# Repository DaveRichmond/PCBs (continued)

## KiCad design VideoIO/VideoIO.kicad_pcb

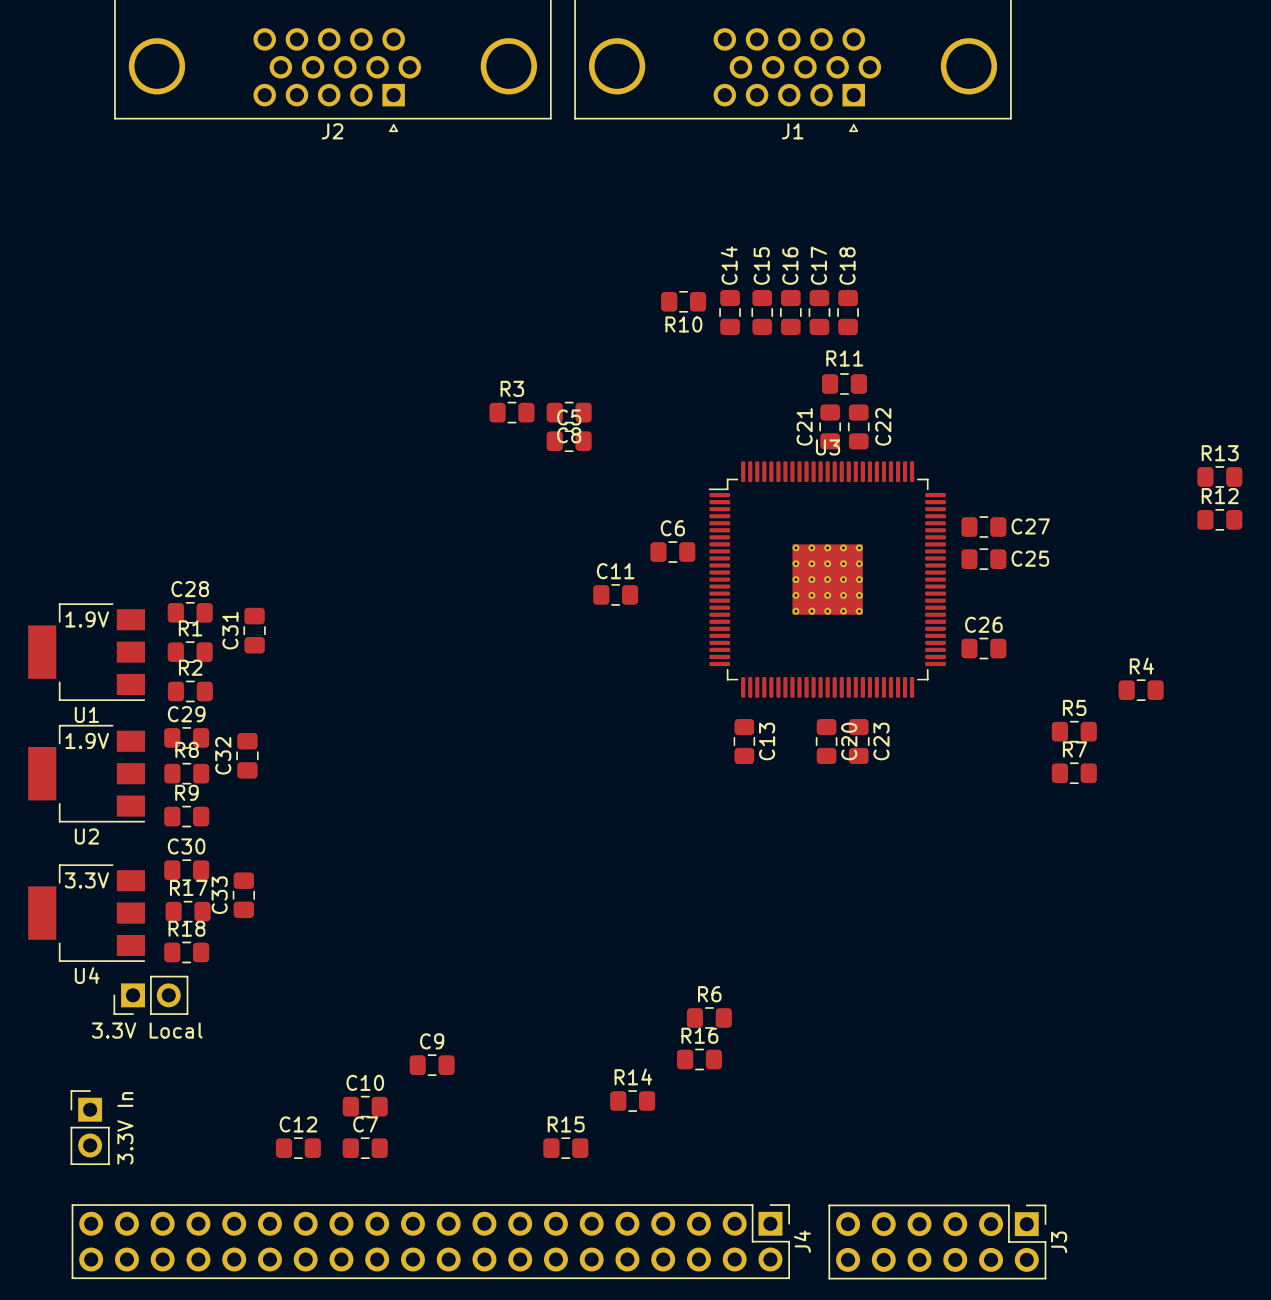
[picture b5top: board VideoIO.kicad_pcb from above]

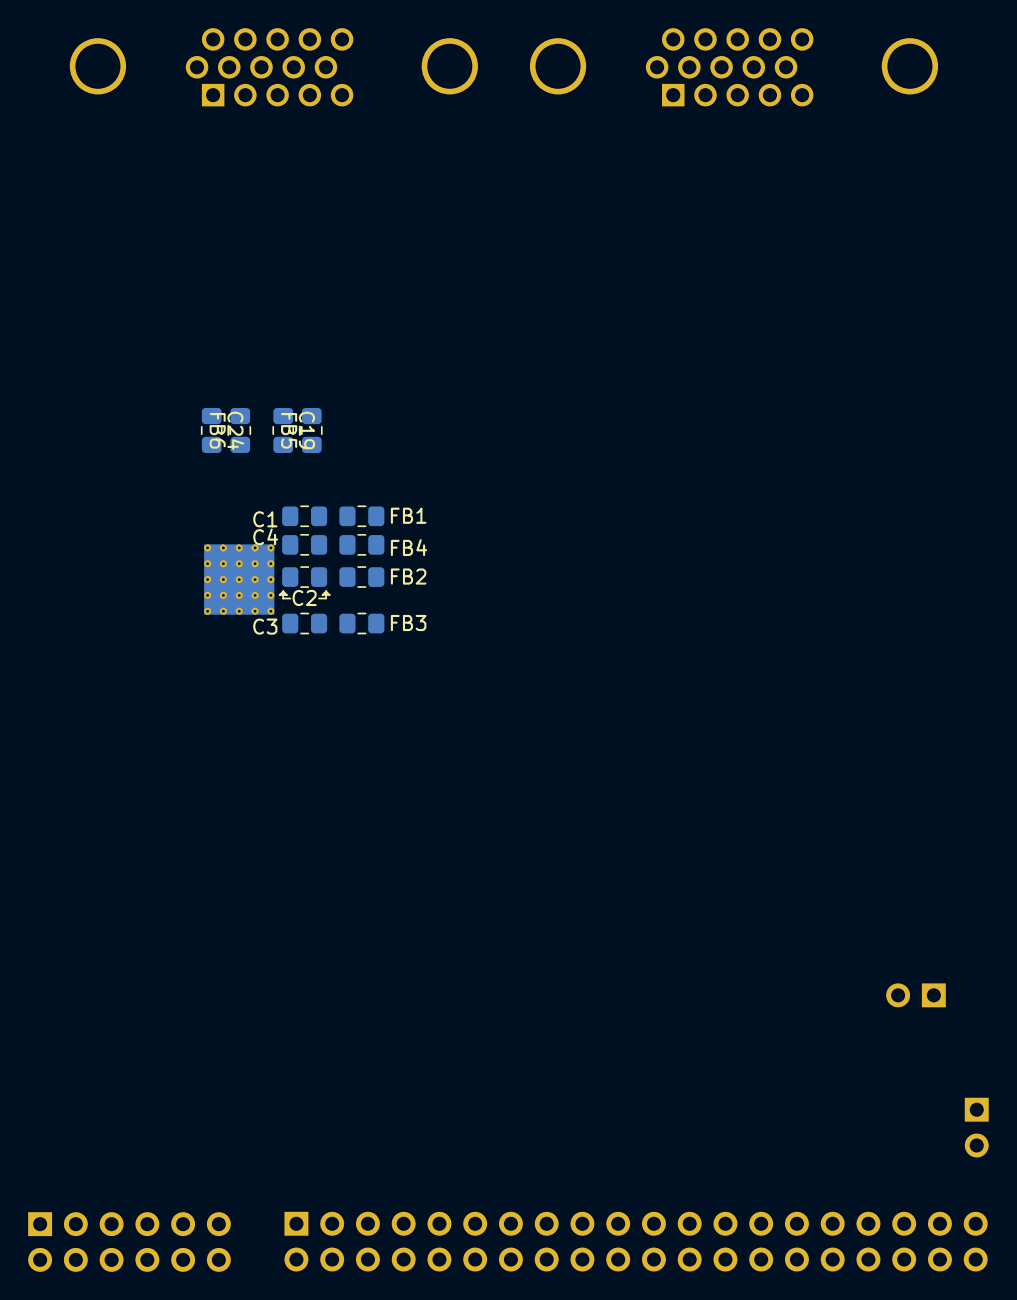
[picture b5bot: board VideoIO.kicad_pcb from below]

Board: 2 copper layers, 67 parts (12 on the bottom side), 84 nets, no tracks yet.

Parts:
C1, C2, C3, C4, C5, C6, C7, C10, C12, C13, C14, C19, C20, C22, C23, C24, C25, C26, C27: 100n; C_0805_2012Metric_Pad1.15x1.40mm_HandSolder
C8, C15, C17: 1n; C_0805_2012Metric_Pad1.15x1.40mm_HandSolder
C9, C11, C16, C18: 10n; C_0805_2012Metric_Pad1.15x1.40mm_HandSolder
C21: 4.7n; C_0805_2012Metric_Pad1.15x1.40mm_HandSolder
C28, C29, C30: C; C_0805_2012Metric_Pad1.15x1.40mm_HandSolder
C31, C32, C33: 10u; C_0805_2012Metric_Pad1.18x1.45mm_HandSolder
FB1, FB2, FB3, FB4, FB5, FB6: Ferrite_Bead_Small; L_0805_2012Metric_Pad1.15x1.40mm_HandSolder
J1, J2: DB15_Male_HighDensity; DSUB-15-HD_Male_Horizontal_P2.29x1.98mm_EdgePinOffset3.03mm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
J3: Conn_02x06_Odd_Even; PinHeader_2x06_P2.54mm_Vertical
J4: Conn_02x20_Odd_Even; PinHeader_2x20_P2.54mm_Vertical
JP1, JP2: Jumper; PinHeader_1x02_P2.54mm_Vertical
R1, R8, R17: 10k; R_0805_2012Metric_Pad1.15x1.40mm_HandSolder
R2, R9: 3.6k; R_0805_2012Metric_Pad1.15x1.40mm_HandSolder
R3, R4, R5, R6, R7, R10: 75R; R_0805_2012Metric_Pad1.15x1.40mm_HandSolder
R11: 1.5k; R_0805_2012Metric_Pad1.15x1.40mm_HandSolder
R12, R13, R14, R15, R16: 2.2k; R_0805_2012Metric_Pad1.15x1.40mm_HandSolder
R18: 12k; R_0805_2012Metric_Pad1.15x1.40mm_HandSolder
U1, U2, U4: AMS1117; SOT-223-3_TabPin2
U3: TVP7002; TQFP-100-1EP_14x14mm_P0.5mm_EP5x5mm_ThermalVias

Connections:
+1V8: C20.1, C27.1, R1.1, U1.2, U3.39, U3.69
+3V3: C13.1, C23.1, C25.1, C26.1, FB2.2, FB5.2, JP1.2, JP2.1, R12.1, R13.1, U3.26, U3.41, U3.53, U3.66
+5V: C28.1, C29.1, C30.1, J4.2, U1.3, U2.3, U4.3
/B0: J4.23, U3.38
/B1: J4.24, U3.37
/B2: J4.25, U3.36
/B3: J4.26, U3.35
/B4: J4.27, U3.34
/B5: J4.28, U3.33
/B6: J4.29, U3.32
/B7: J4.30, U3.31
/B8: J4.31, U3.30
/B9: J4.32, U3.29
/G0: J4.13, U3.52
/G1: J4.14, U3.51
/G2: J4.15, U3.50
/G3: J4.16, U3.49
/G4: J4.17, U3.48
/G5: J4.18, U3.47
/G6: J4.19, U3.46
/G7: J4.20, U3.45
/G8: J4.21, U3.44
/G9: J4.22, U3.43
/R0: J4.3, U3.65
/R1: J4.4, U3.64
/R2: J4.5, U3.63
/R3: J4.6, U3.62
/R4: J4.7, U3.61
/R5: J4.8, U3.59
/R6: J4.9, U3.58
/R7: J4.10, U3.57
/R8: J4.11, U3.56
/R9: J4.12, U3.55
/VGA1_B: C12.1, J1.3, R7.2
/VGA1_G: C5.1, C8.2, J1.2, R3.2
/VGA1_HSYNC: J1.13, U3.81
/VGA1_R: C10.1, J1.1, R6.2
/VGA1_VSYNC: J1.14, U3.78
/VGA2_B: C7.1, J2.3, R5.2
/VGA2_G: C14.2, C15.2, J2.2, R10.1
/VGA2_HSYNC: J2.13, U3.82
/VGA2_R: C6.1, J2.1, R4.2
/VGA2_VSYNC: J2.14, U3.79
CLK_27M: J3.1, U3.80
FID: J3.12, U3.22
GND: C1.1, C2.1, C3.1, C4.1, C9.2, C11.2, C13.2, C16.1, C17.1, C18.1, C19.1, C20.2, C23.2, C24.1, C25.2, C26.2, C27.2, C28.2, C29.2, C30.2, C31.2, C32.2, C33.2, J1.5, J1.6, J1.7, J1.8, J1.10, J2.5, J2.6, J2.7, J2.8, J2.10, J3.11, J4.1, J4.37, J4.38, R2.2, R3.1, R4.1, R5.1, R6.1, R7.1, R9.2, R10.2, R14.1, R15.1, R16.1, R18.2, U3.3, U3.5, U3.8, U3.12, U3.15, U3.20, U3.21, U3.27, U3.40, U3.42, U3.54, U3.60, U3.67, U3.68, U3.73, U3.76, U3.77, U3.83, U3.86, U3.90, U3.91, U3.92, U3.95
GSYNC: J3.10, U3.25
HSYNC: J3.8, J4.33, U3.24
unnamed: C1.2, FB1.1, U3.4
unnamed: C2.2, FB2.1, U3.13, U3.14
unnamed: C3.2, FB3.1, U3.19
unnamed: C4.2, FB4.1, U3.6, U3.7
unnamed: C5.2, U3.2
unnamed: C6.2, U3.10
unnamed: C7.2, U3.17
unnamed: C8.1, U3.1
unnamed: C9.1, U3.9
unnamed: C10.2, U3.11
unnamed: C11.1, U3.16
unnamed: C12.2, U3.18
unnamed: C14.1, U3.100
unnamed: C15.1, U3.99
unnamed: C16.2, U3.98
unnamed: C17.2, U3.97
unnamed: C18.2, U3.96
unnamed: C19.2, FB5.1, U3.93, U3.94
unnamed: C21.1, R11.1, U3.89
unnamed: C21.2, U3.88
unnamed: C22.1, R11.2
unnamed: C22.2, U3.87
unnamed: C24.2, FB6.1, U3.84, U3.85
unnamed: C31.1, R1.2, R2.1, U1.1
unnamed: C32.1, R8.2, R9.1, U2.1
unnamed: C33.1, R17.2, R18.1, U4.1
unnamed: J4.39, J4.40, JP2.2
unnamed: JP1.1, R17.1, U4.2
PCLK: J3.2, U3.28
PWDN: J3.4, R16.2, U3.70
RESET: J3.7, R14.2, U3.71
SCL: J3.5, J4.36, R13.2, U3.74
SDA: J3.3, J4.35, R12.2, U3.75
TMS: J3.9, R15.2, U3.72
VDDA: FB1.2, FB3.2, FB4.2, FB6.2, R8.1, U2.2
VSYNC: J3.6, J4.34, U3.23

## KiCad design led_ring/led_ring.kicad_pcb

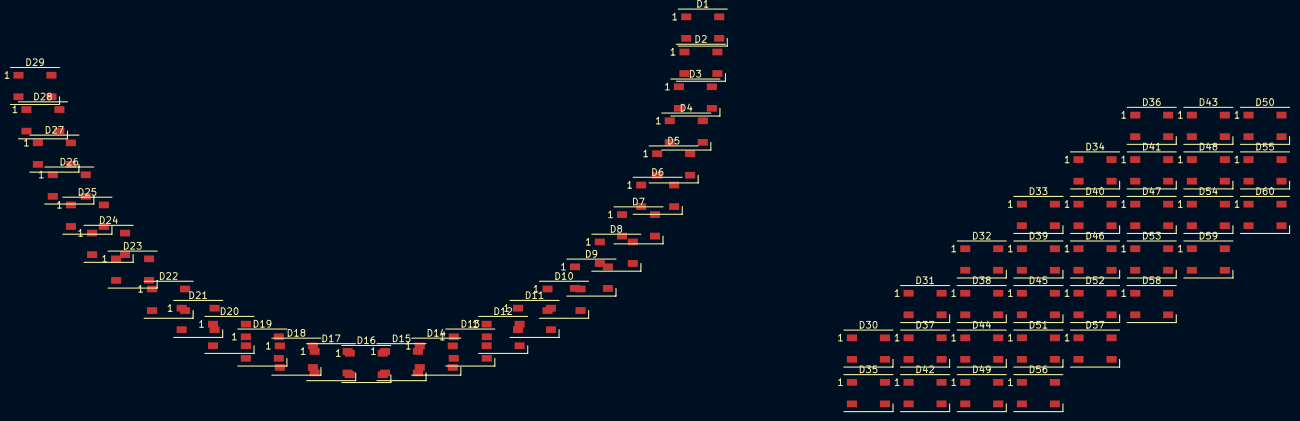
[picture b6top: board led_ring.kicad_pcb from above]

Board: 2 copper layers, 60 parts (0 on the bottom side), 61 nets, no tracks yet.

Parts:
D1, D2, D3, D4, D5, D6, D7, D8, D9, D10, D11, D12, D13, D14, D15, D16, D17, D18, D19, D20, D21, D22, D23, D24, D25, D26, D27, D28, D29, D30, D31, D32, D33, D34, D35, D36, D37, D38, D39, D40, D41, D42, D43, D44, D45, D46, D47, D48, D49, D50, D51, D52, D53, D54, D55, D56, D57, D58, D59, D60: WS2812B; LED_WS2812B_PLCC4_5.0x5.0mm_P3.2mm

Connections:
+5V: D1.1, D2.1, D3.1, D4.1, D5.1, D6.1, D7.1, D8.1, D9.1, D10.1, D11.1, D12.1, D13.1, D14.1, D15.1, D16.1, D17.1, D18.1, D19.1, D20.1, D21.1, D22.1, D23.1, D24.1, D25.1, D26.1, D27.1, D28.1, D29.1, D30.1, D31.1, D32.1, D33.1, D34.1, D35.1, D36.1, D37.1, D38.1, D39.1, D40.1, D41.1, D42.1, D43.1, D44.1, D45.1, D46.1, D47.1, D48.1, D49.1, D50.1, D51.1, D52.1, D53.1, D54.1, D55.1, D56.1, D57.1, D58.1, D59.1, D60.1
GND: D1.3, D2.3, D3.3, D4.3, D5.3, D6.3, D7.3, D8.3, D9.3, D10.3, D11.3, D12.3, D13.3, D14.3, D15.3, D16.3, D17.3, D18.3, D19.3, D20.3, D21.3, D22.3, D23.3, D24.3, D25.3, D26.3, D27.3, D28.3, D29.3, D30.3, D31.3, D32.3, D33.3, D34.3, D35.3, D36.3, D37.3, D38.3, D39.3, D40.3, D41.3, D42.3, D43.3, D44.3, D45.3, D46.3, D47.3, D48.3, D49.3, D50.3, D51.3, D52.3, D53.3, D54.3, D55.3, D56.3, D57.3, D58.3, D59.3, D60.3
unnamed: D1.2, D2.4
unnamed: D2.2, D3.4
unnamed: D3.2, D4.4
unnamed: D4.2, D5.4
unnamed: D5.2, D6.4
unnamed: D6.2, D7.4
unnamed: D7.2, D8.4
unnamed: D8.2, D9.4
unnamed: D10.2, D11.4
unnamed: D9.2, D10.4
unnamed: D11.2, D12.4
unnamed: D12.2, D13.4
unnamed: D13.2, D14.4
unnamed: D14.2, D15.4
unnamed: D15.2, D16.4
unnamed: D16.2, D17.4
unnamed: D17.2, D18.4
unnamed: D18.2, D19.4
unnamed: D19.2, D20.4
unnamed: D20.2, D21.4
unnamed: D21.2, D22.4
unnamed: D22.2, D23.4
unnamed: D23.2, D24.4
unnamed: D24.2, D25.4
unnamed: D25.2, D26.4
unnamed: D26.2, D27.4
unnamed: D27.2, D28.4
unnamed: D28.2, D29.4
unnamed: D29.2, D30.4
unnamed: D30.2, D31.4
unnamed: D31.2, D32.4
unnamed: D32.2, D33.4
unnamed: D33.2, D34.4
unnamed: D34.2, D35.4
unnamed: D35.2, D36.4
unnamed: D36.2, D37.4
unnamed: D37.2, D38.4
unnamed: D38.2, D39.4
unnamed: D39.2, D40.4
unnamed: D40.2, D41.4
unnamed: D41.2, D42.4
unnamed: D42.2, D43.4
unnamed: D43.2, D44.4
unnamed: D44.2, D45.4
unnamed: D45.2, D46.4
unnamed: D46.2, D47.4
unnamed: D47.2, D48.4
unnamed: D48.2, D49.4
unnamed: D49.2, D50.4
unnamed: D50.2, D51.4
unnamed: D51.2, D52.4
unnamed: D52.2, D53.4
unnamed: D53.2, D54.4
unnamed: D54.2, D55.4
unnamed: D55.2, D56.4
unnamed: D56.2, D57.4
unnamed: D57.2, D58.4
unnamed: D58.2, D59.4
unnamed: D59.2, D60.4

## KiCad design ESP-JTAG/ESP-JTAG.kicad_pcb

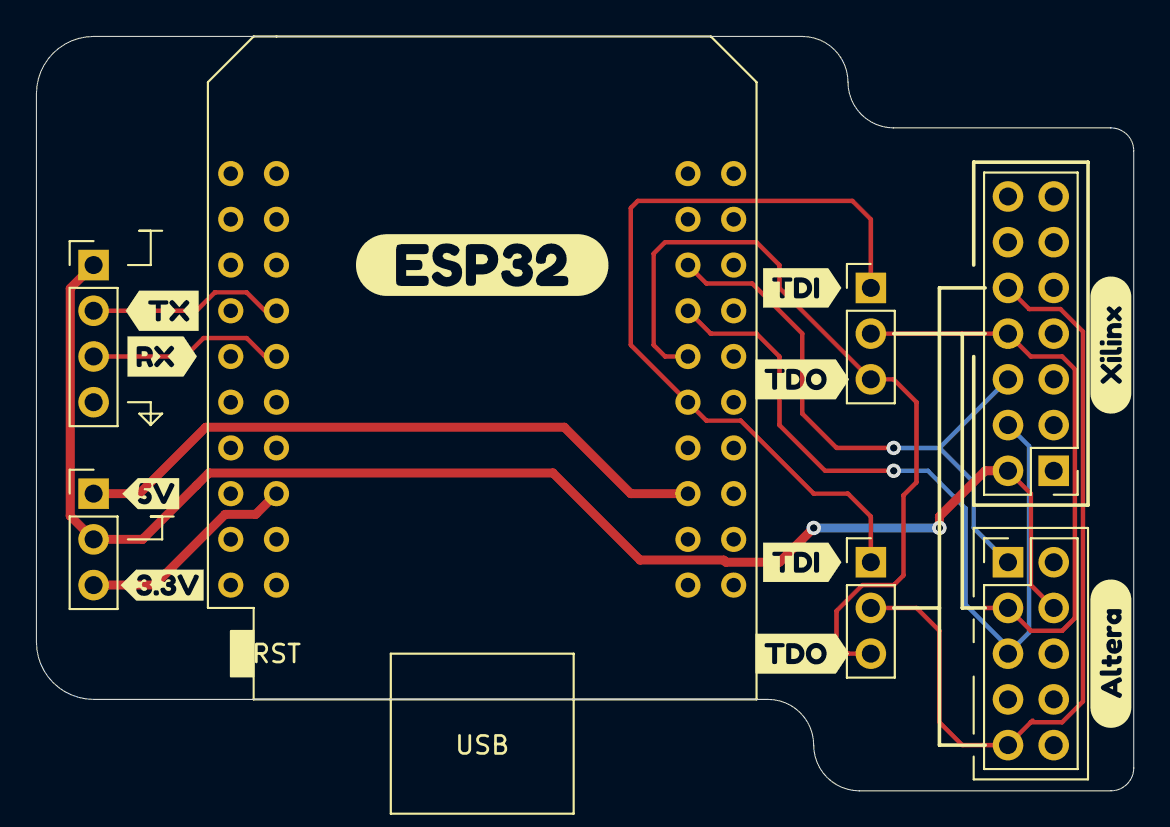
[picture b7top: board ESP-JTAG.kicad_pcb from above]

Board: 2 copper layers, 61.0 x 41.9 mm, 18 parts (0 on the bottom side), 12 nets.

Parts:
J1: Conn_02x07_Odd_Even; PinHeader_2x07_P2.54mm_Vertical
J2: Conn_02x05_Odd_Even; PinHeader_2x05_P2.54mm_Vertical
J3, J4, J5: Conn_01x03; PinHeader_1x03_P2.54mm_Vertical
J6: Conn_01x04; PinHeader_1x04_P2.54mm_Vertical
U1: mini_esp32; ESP32_mini
kibuzzard-61C935D1: G***; kibuzzard-61C935D1
kibuzzard-61C937B7: G***; kibuzzard-61C937B7
kibuzzard-61C9374F: G***; kibuzzard-61C9374F
kibuzzard-61C93722: G***; kibuzzard-61C93722
kibuzzard-61C93731: G***; kibuzzard-61C93731
kibuzzard-61C93744: G***; kibuzzard-61C93744
kibuzzard-61C93764: G***; kibuzzard-61C93764
kibuzzard-61C93777: G***; kibuzzard-61C93777
kibuzzard-61C93796: G***; kibuzzard-61C93796
svg2mod, svg2mod#2: G***; label

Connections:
+3V3: J3.3, U1.16
+5V: J3.1, U1.35
/TCK: J1.6, J2.1, U1.25
/TDI: J4.1, J5.1, U1.31
/TDO: J4.3, J5.3, U1.29
/TMS: J1.4, J2.5, U1.27
/U_RX: J6.3, U1.10
/U_TX: J6.2, U1.8
GND: J1.1, J1.3, J1.5, J1.7, J1.9, J1.11, J1.13, J2.2, J2.10, J6.4, U1.1, U1.22, U1.33
unnamed: J1.8, J2.3, J4.2
unnamed: J1.10, J2.9, J5.2
VCC: J1.2, J2.4, J3.2, J6.1

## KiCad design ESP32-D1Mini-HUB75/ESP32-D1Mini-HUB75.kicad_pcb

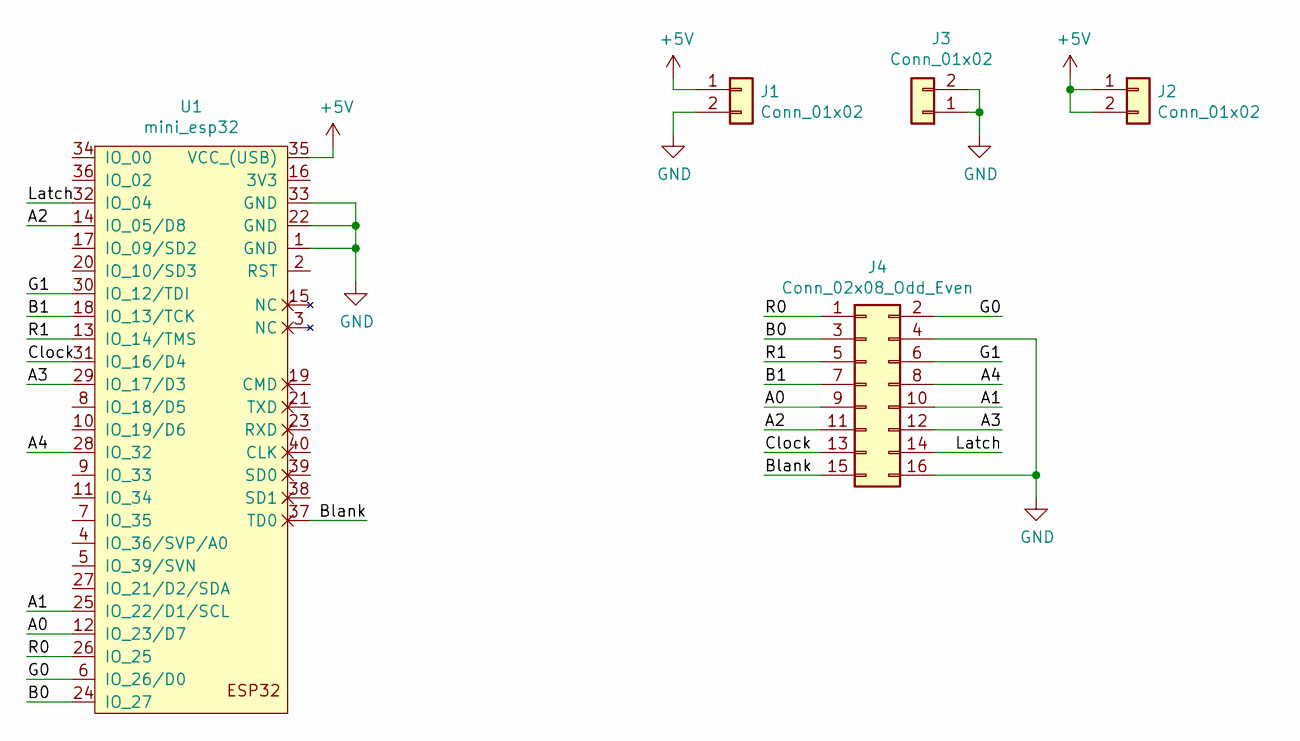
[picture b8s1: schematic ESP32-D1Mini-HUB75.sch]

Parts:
J1: Conn_01x02; KF8500-2P
J2, J3: Conn_01x02; TerminalBlock_bornier-2_P5.08mm
J4: Conn_02x08_Odd_Even; PinHeader_2x08_P2.54mm_Vertical
U1: mini_esp32; ESP32_mini

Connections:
+5V: J1.1, J2.1, J2.2, U1.35 (VCC_(USB))
/A0: J4.9, U1.12 (IO_23/D7)
/A1: J4.10, U1.25 (IO_22/D1/SCL)
/A2: J4.11, U1.14 (IO_05/D8)
/A3: J4.12, U1.29 (IO_17/D3)
/A4: J4.8, U1.28 (IO_32)
/B0: J4.3, U1.24 (IO_27)
/B1: J4.7, U1.18 (IO_13/TCK)
/Blank: J4.15, U1.37 (TD0)
/Clock: J4.13, U1.31 (IO_16/D4)
/G0: J4.2, U1.6 (IO_26/D0)
/G1: J4.6, U1.30 (IO_12/TDI)
/Latch: J4.14, U1.32 (IO_04)
/R0: J4.1, U1.26 (IO_25)
/R1: J4.5, U1.13 (IO_14/TMS)
GND: J1.2, J3.1, J3.2, J4.4, J4.16, U1.1 (GND), U1.22 (GND), U1.33 (GND)

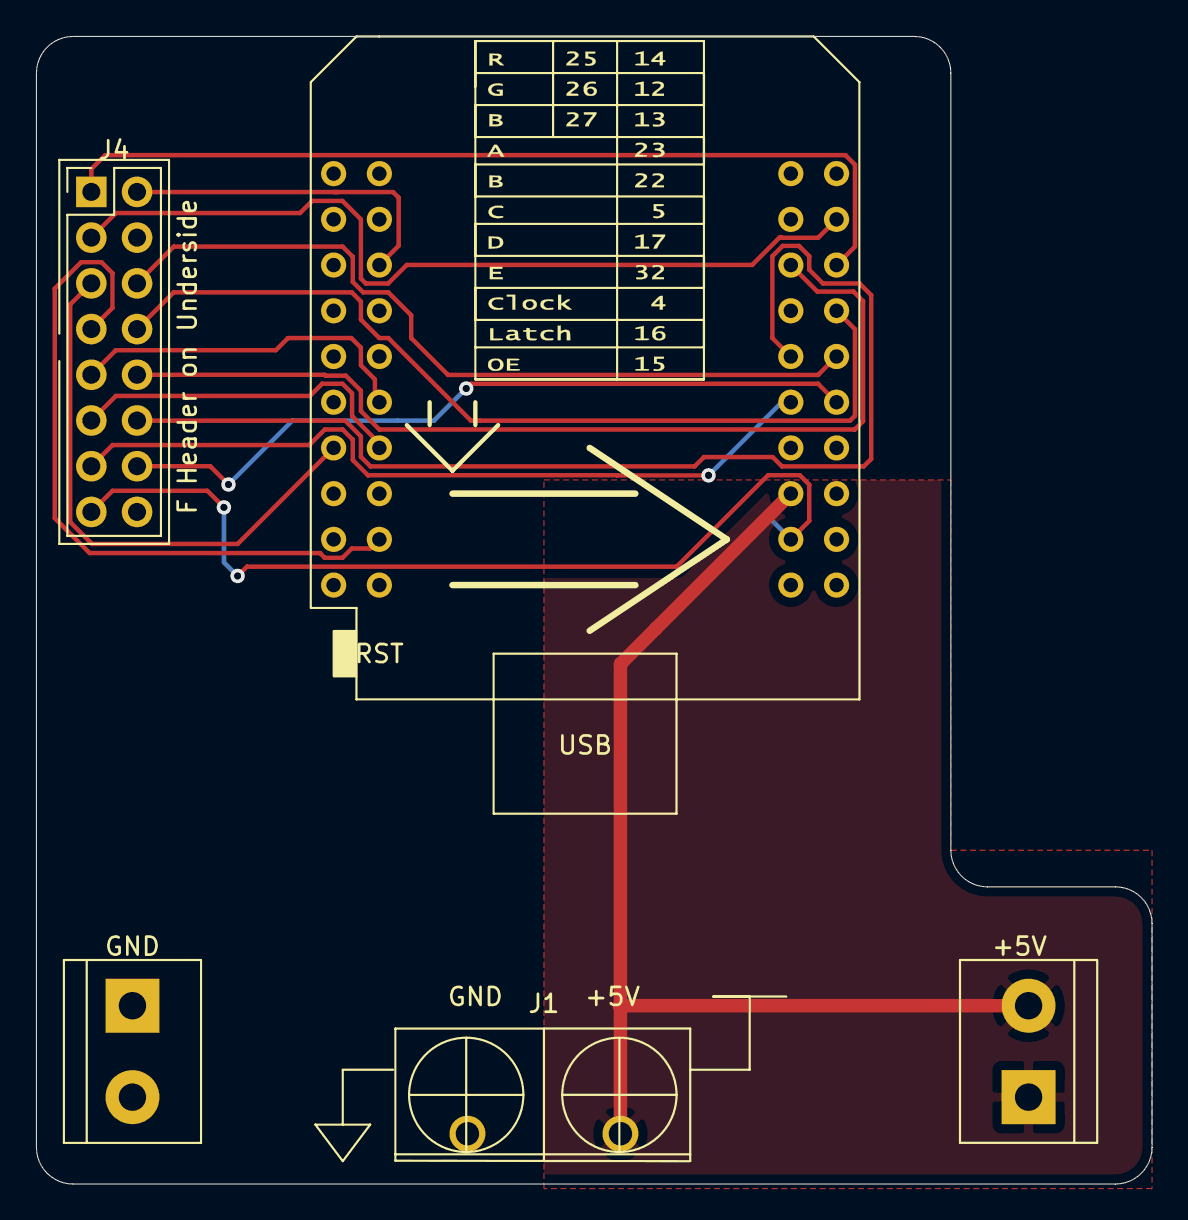
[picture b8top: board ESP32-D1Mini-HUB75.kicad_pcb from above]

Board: 2 copper layers, 62.0 x 63.8 mm, 6 parts (0 on the bottom side), 16 nets.

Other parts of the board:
Ref**: Val**; pinout

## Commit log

2019-12-01 SWD Breakout
    ST-Linkv2 clone -> bluepill (and compatible SWD headers)
2019-12-11 SWD Breakout updates
2019-12-11 Bluepill-BitBlaster breakout board
    Provides a breakout from the bluepill board to an altera bitblaster compatible interface with appropriate firmware
2019-12-11 M68K to Nucleo144 Adapter
    Allows an STM32 on Nucleo144 to bitbang an m68k bus directly to a dip68 M68000
2019-12-11 Archive of current gerber files
2019-12-26 Added backup files to ignore
2020-01-28 D1 LED Matrix start
    documentation for parts needed, and initial footprint for screw terminal
2020-01-28 ESP P10 Gerbers rev3
2020-01-28 QMTech SRAM Adapter
    Initial prototype
2020-04-04 Added olimex libraries
2020-04-04 Changed level shifter package on M68k board
2020-04-04 Updated m68k outputs
2020-04-12 Added STM32 Energy monitor
2020-04-12 Energy monitor gerbers generated
2020-04-12 Added 1.4" LCD to energymonitor
2020-05-27 Heater Array PCB
2020-06-05 Video Input Board
2020-06-05 Missed component values
2020-06-17 More work on TVP7002/VideoIO Board
2020-06-17 Gerbers of SRAM board designed in easyeda
2020-06-17 More work on video io board
2020-06-17 Is this file important?
2021-01-29 Add documentation
2021-01-29 Gotek to PS/2 Floppy Adapter Schematic
2021-03-11 initial minikeyboard commit
2021-03-12 Added 411CE Blackpill to minikeyboard
2021-03-20 moved submodules around
2021-03-20 fixed minikeyboard after moving libraries around
2021-03-21 esp32 hub75 adapter
2021-03-22 mini keyboard layout
2021-04-18 updated screw terminal in esp32 hub75 board to use 8.5mm terminal that better suits the power cable that comes with the matrices
2021-04-18 mini keyboard progress
2021-04-18 more gotek to ps2 adapter progress
2021-04-18 added plane to +5V for the power distribution between screw terminals
2021-04-20 moved user info text to using kibuzzard generated labels
2021-04-29 changed minikeyboard diodes and generated gerbers
2021-04-29 gerbers for next order cycle
2021-05-05 addressable led based seven segment display. Quick hack, maybe submit the gerbers one day
2021-05-09 added thirtythreeforty's libraries for pcb usb footprint
2021-05-09 missed change?
2021-05-09 Missed gotek updates
2021-05-09 more missed updates - gerber exports maybe
2021-12-10 starting on FPGA-SCSI Converter/Sniffer
2021-12-10 kicad artifacts
2021-12-10 scsi schematic work
2021-12-27 ESP-JTAG (xvc) adapter
2022-08-23 Sun keyboard interface
    - e78 breakout also partially added in. Ooops @ unclean commits
2023-04-10 Misc missed changes? Been a while since I really looked
2023-07-05 routed e78 breakout
2023-07-05 version from which e78 breakout was generated
2023-07-05 version from which sun kbd interface was generated
2024-01-09 initial commit of pi serial shim hat. No routing completed yet
